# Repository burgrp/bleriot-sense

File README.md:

# BleRiot Sense

BleRiot Sense is a compact single-sensor BleRiot node built around a
`PY32F003L16S6TU` microcontroller and a PAN2110 long-range 2.4 GHz radio. Its
sensor input is configured at assembly time for one of four uses:

- A 10 kΩ B3950 NTC thermistor.
- A pulse-output flow sensor such as the YF-B10.
- A pressure sensor with a driven 0.5-5 V analog output.
- An externally powered DS18B20 digital thermometer.

The assembly population and the firmware mode must agree. The hardware does not
switch sensor modes electronically at runtime.

## Repository layout

| Path | Description |
|---|---|
| [`board/bleriot-sense.kicad_pro`](board/bleriot-sense.kicad_pro) | `PY32F003L16S6TU` hardware |
| [`fw/`](fw/README.md) | Importable Sense firmware and board-owned build profile |
| [`fw/cmd/dev/`](fw/cmd/dev/) | Local inventory and BleRiot CLI |
| [`ANALOG-INPUT.md`](ANALOG-INPUT.md) | Configurable input circuit, populations, calculations, protection, and layout |
| [`sub/hw-kicad/`](sub/hw-kicad) | Shared KiCad symbols and footprints, included as a Git submodule |

## Sensor modes

| Mode | Node measurement | Registry value |
|---|---|---|
| NTC | Averaged 12-bit ADC code | Temperature in °C |
| Flow | Rising-edge pulse count | Frequency in Hz and cumulative pulse count |
| Pressure | Averaged 12-bit ADC code | Reconstructed sensor-output voltage in V |
| DS18B20 | Up to 20 signed Q12.4 scratchpad values | Temperature registers in °C |

See [`ANALOG-INPUT.md`](ANALOG-INPUT.md) before assembling a board. It defines
the required values for `AR1`, `AR2`, `AR3`, and `AC1`, including the two
alternative flow-sensor output circuits.

The pressure transfer function and flow K-factor depend on the exact sensor.
The hub currently exposes pressure input voltage and flow frequency without
assuming undocumented sensor calibration constants.

## Firmware status

[`fw`](fw/README.md) targets the `PY32F003L16S6TU` and uses `PA0` for
the universal sensor input. The NTC path has been verified end to end on
hardware through the ADC, PAN2110 radio, MCP2210 hub dongle, BleRiot hub,
conversion layer, and Registry. The single-sensor DS18B20 path has also been
verified end to end through its 1-Wire bus and the same radio/Registry path;
multidrop behavior still requires hardware validation. Flow and pressure support build and have
host-side conversion coverage but still require mode-specific hardware tests.

DS18B20 firmware prints discovered ROM IDs over RTT at boot. A single sensor
needs no configured ID; multidrop inventories map each temperature register to
an explicit ID. See the firmware README for configuration and timing details.

The upstream TinyGo `py32f003x6` target provides the required 1 KiB system
stack. The firmware runs without a task scheduler. See the firmware README for
pin assignments, first-boot option-byte handling, configuration, and memory
constraints.

## Getting started

Initialize the shared KiCad library after cloning:

```sh
git submodule update --init --recursive
```

Open the hardware project in KiCad:

```sh
kicad board/bleriot-sense.kicad_pro
```

Configure `sensorMode` in
[`fw/cmd/dev/main.go`](fw/cmd/dev/main.go), then test and build the firmware:

```sh
go -C fw test ./...
go -C fw run ./cmd/dev node build --name sense
```

Flash with a supported SWD probe:

```sh
go -C fw run ./cmd/dev node build --name sense --flash --rtt
```

With a Registry server running, start the hub in a separate terminal:

```sh
go -C fw run ./cmd/dev hub --registry http://localhost:8080 --diagnostics rf
```

For an NTC-configured node, read live temperatures:

```bash
export REGISTRY=http://localhost:8080
reg get sense.temperature --stay
```

## Toolchain

- KiCad 10 for the hardware projects.
- Go 1.25.2 or newer for the firmware inventory, generator, tests, and hub.
- TinyGo with the Puya `py32f003x6` target.
- pyOCD with the Puya CMSIS pack and a supported SWD probe.
- An MCP2210/PAN2110 BleRiot hub dongle for RF operation.
- The [`reg`](https://github.com/burgrp/reg) Registry service and CLI.

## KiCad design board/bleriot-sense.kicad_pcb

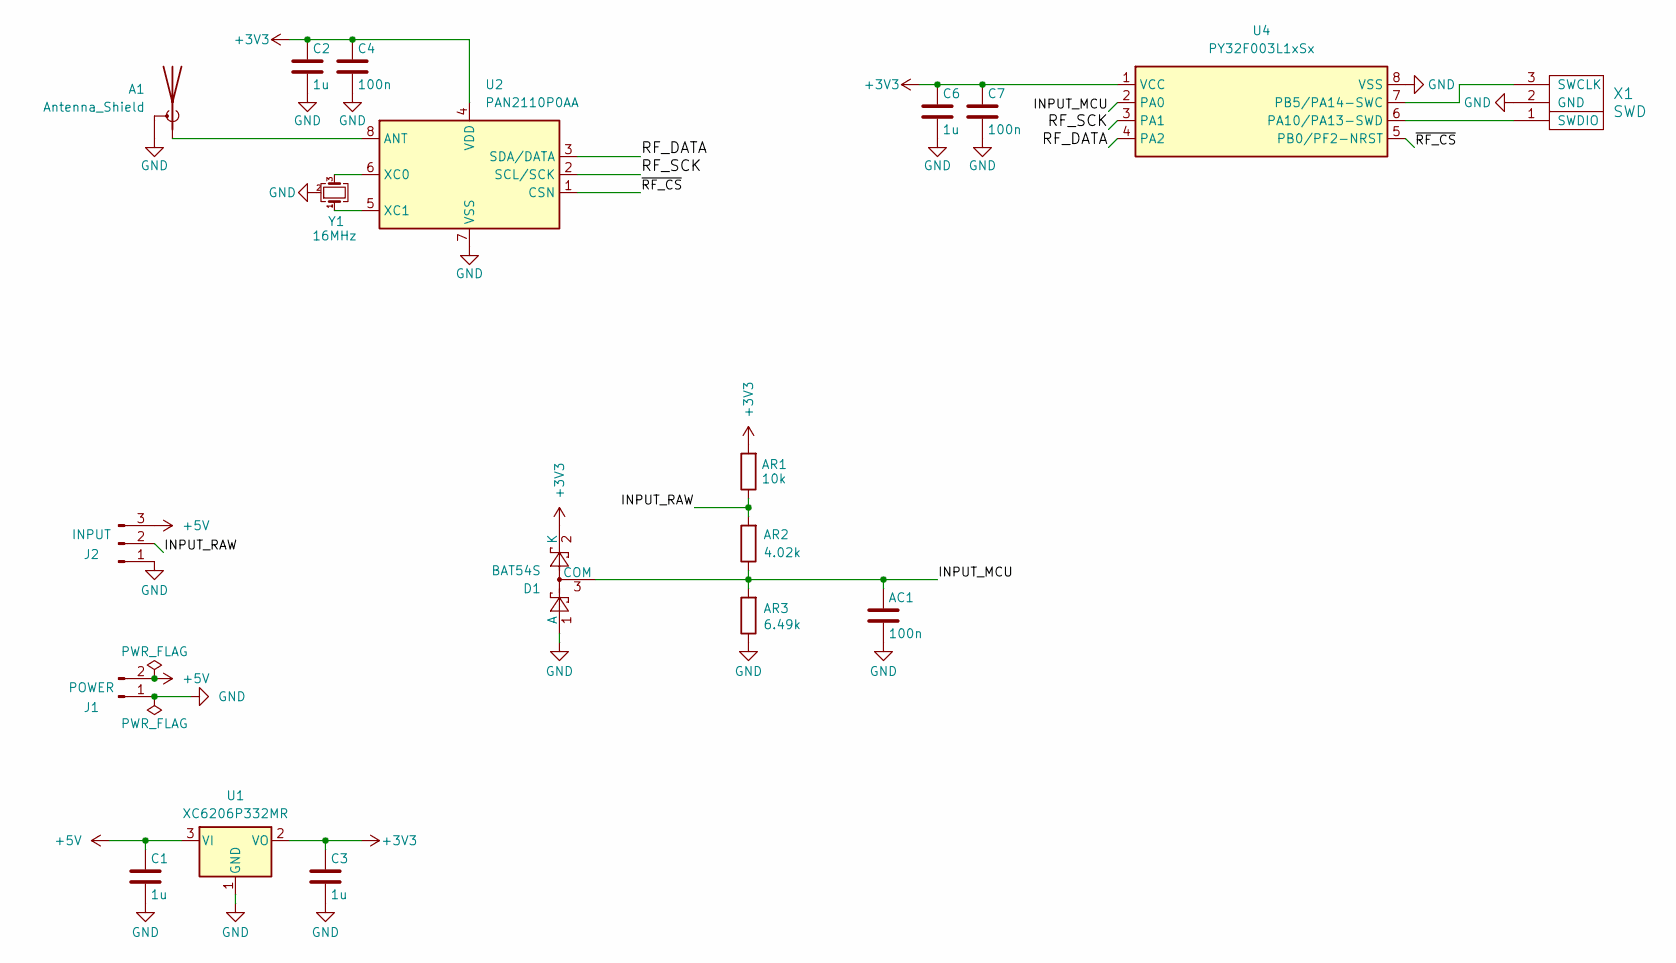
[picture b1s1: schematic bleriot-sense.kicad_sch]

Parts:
A1: Antenna_Shield; Texas_SWRA117D_2.4GHz_Left
AC1: 100n; C_0805_2012Metric
AR1: 10k; R_0805_2012Metric
AR2: 4.02k; R_0805_2012Metric
AR3: 6.49k; R_0805_2012Metric
C1, C2, C3, C6: 1u; C_0805_2012Metric
C4, C7: 100n; C_0805_2012Metric
D1: BAT54S; SOT-23
J1: POWER; PhoenixContact_MSTBA_2,5_2-G_1x02_P5.00mm_Horizontal
J2: INPUT; PhoenixContact_MSTBA_2,5_3-G_1x03_P5.00mm_Horizontal
U1: XC6206P332MR; SOT-23-3
U2: PAN2110P0AA; SOIC-8_3.9x4.9mm_P1.27mm
U4: PY32F003L1xSx; SOIC-8_3.9x4.9mm_P1.27mm
X1: SWD
Y1: 16MHz; Crystal_SMD_3225-4Pin_3.2x2.5mm

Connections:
+3V3: AR1.2, C2.1, C3.1, C4.1, C6.1, C7.1, D1.2 (K), U1.2 (VO), U2.4 (VDD), U4.1 (VCC)
+5V: C1.1, J1.2, J2.3, U1.3 (VI)
/INPUT_MCU: AC1.1, AR2.1, AR3.2, D1.3 (COM), U4.2 (PA0)
/INPUT_RAW: AR1.1, AR2.2, J2.2
/RF_DATA: U2.3 (SDA/DATA), U4.4 (PA2)
/RF_SCK: U2.2 (SCL/SCK), U4.3 (PA1)
/~RF_CS: U2.1 (CSN), U4.5 (PB0/PF2-NRST)
GND: A1.2 (Shield), AC1.2, AR3.1, C1.2, C2.2, C3.2, C4.2, C6.2, C7.2, D1.1 (A), J1.1, J2.1, U1.1 (GND), U2.7 (VSS), U4.8 (VSS), X1.2 (GND), Y1.2 (G), Y1.4 (G)
unnamed: A1.1 (A), U2.8 (ANT)
unnamed: U2.6 (XC0), Y1.3
unnamed: U2.5 (XC1), Y1.1
unnamed: U4.6 (PA10/PA13-SWD), X1.1 (SWDIO)
unnamed: U4.7 (PB5/PA14-SWC), X1.3 (SWCLK)

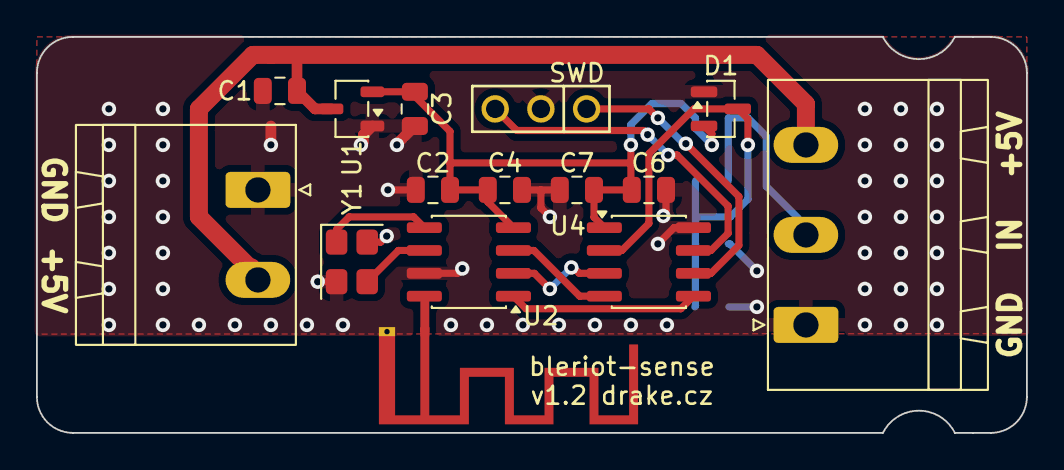
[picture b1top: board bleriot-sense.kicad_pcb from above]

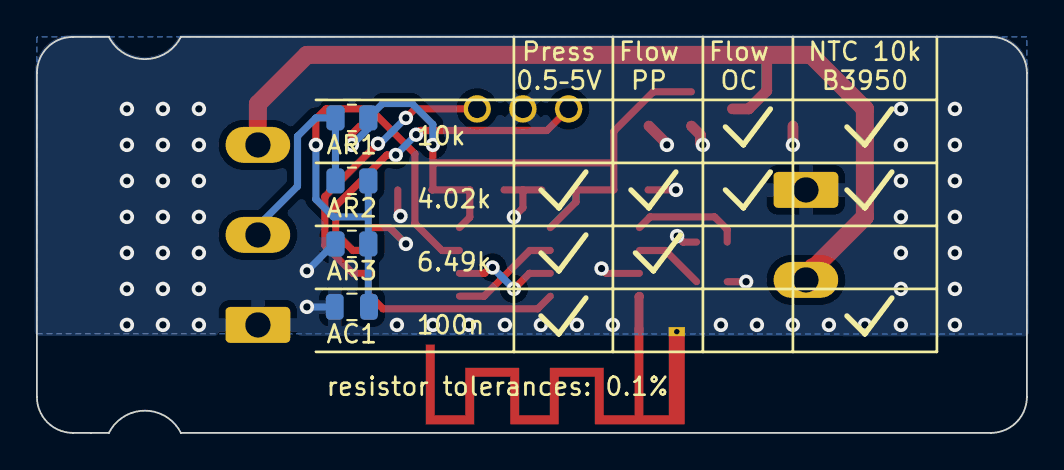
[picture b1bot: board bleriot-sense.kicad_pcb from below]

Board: 2 copper layers, 55.0 x 22.0 mm, 19 parts (4 on the bottom side), 13 nets.

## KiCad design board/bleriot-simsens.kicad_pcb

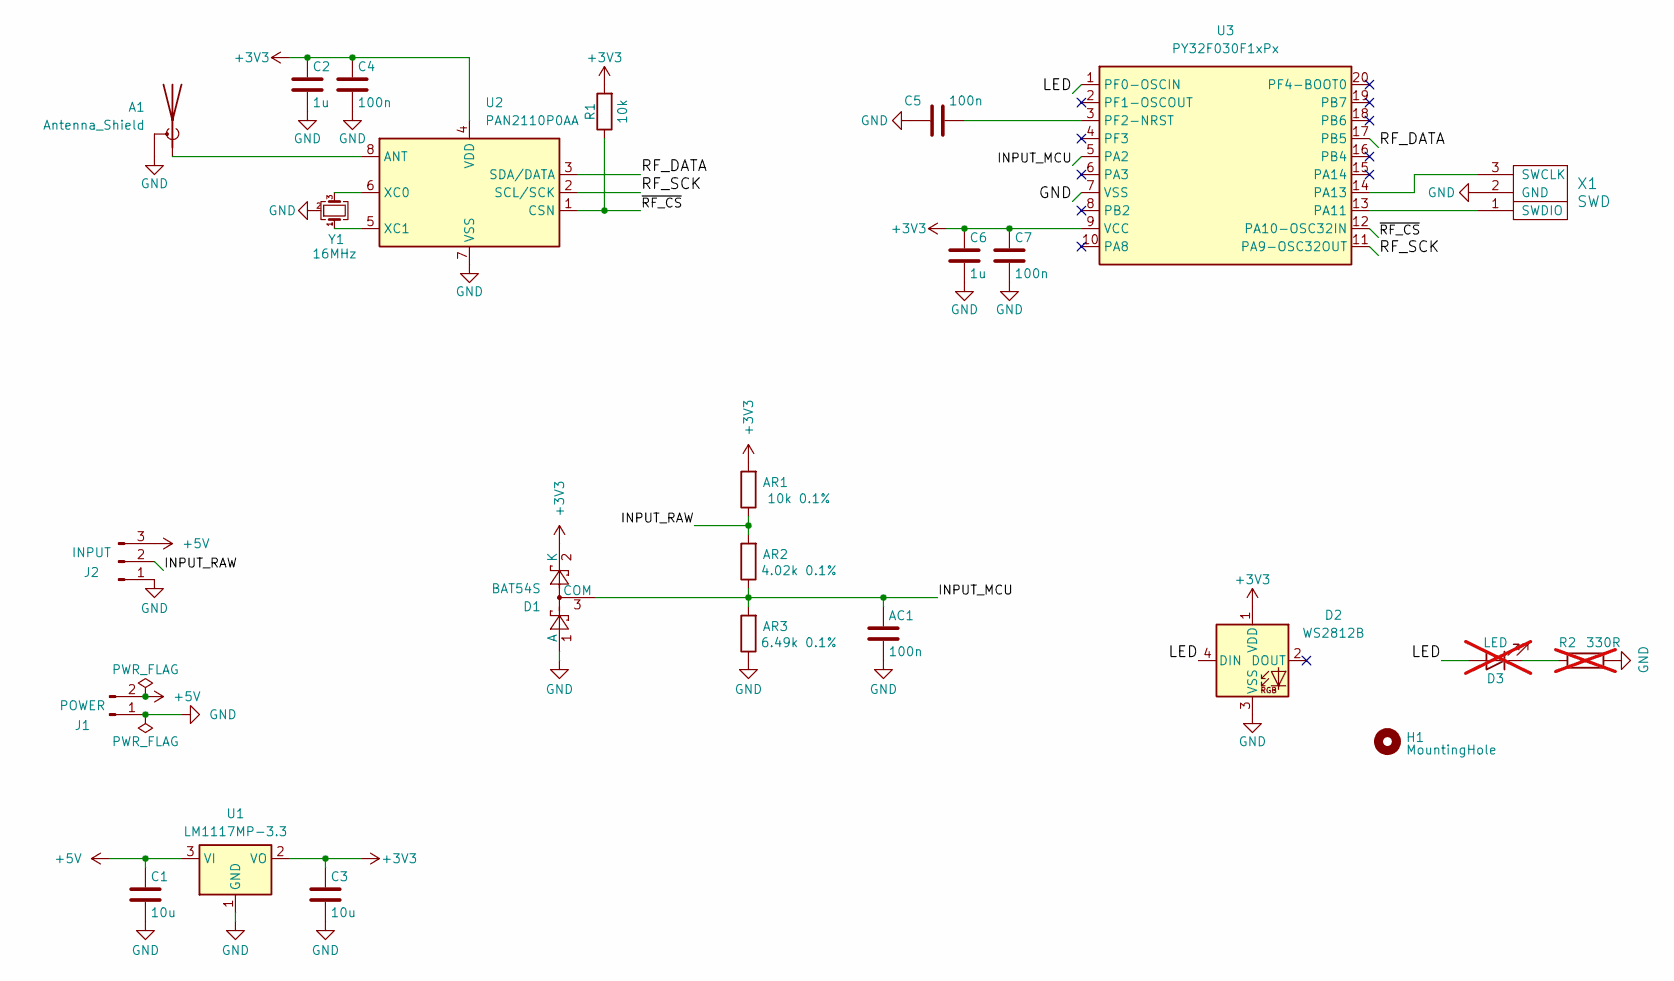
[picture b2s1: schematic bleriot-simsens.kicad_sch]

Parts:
A1: Antenna_Shield; Texas_SWRA117D_2.4GHz_Right
AC1: 100n; C_0805_2012Metric
AR1: 10k 0.1%; R_0805_2012Metric
AR2: 4.02k 0.1%; R_0805_2012Metric
AR3: 6.49k 0.1%; R_0805_2012Metric
C1, C3: 10u; C_0805_2012Metric
C2, C6: 1u; C_0805_2012Metric
C4, C5, C7: 100n; C_0805_2012Metric
D1: BAT54S; SOT-23
D2: WS2812B; LED_WS2812B_PLCC4_5.0x5.0mm_P3.2mm
D3: LED; LED_0805_2012Metric_Pad1.15x1.40mm_HandSolder; not fitted
H1: MountingHole; MountingHole_3.7mm_Pad_Via
J1: POWER; PhoenixContact_MSTBA_2,5_2-G_1x02_P5.00mm_Horizontal
J2: INPUT; PhoenixContact_MSTBA_2,5_3-G_1x03_P5.00mm_Horizontal
R1: 10k; R_0805_2012Metric
R2: 330R; R_0805_2012Metric; not fitted
U1: LM1117MP-3.3; SOT-223-3_TabPin2
U2: PAN2110P0AA; SOIC-8_3.9x4.9mm_P1.27mm
U3: PY32F030F1xPx; TSSOP-20_4.4x6.5mm_P0.65mm
X1: SWD
Y1: 16MHz; Crystal_SMD_3225-4Pin_3.2x2.5mm

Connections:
+3V3: AR1.2, C2.1, C3.1, C4.1, C6.1, C7.1, D1.2 (K), D2.1 (VDD), R1.2, U1.2 (VO), U2.4 (VDD), U3.9 (VCC)
+5V: C1.1, J1.2, J2.3, U1.3 (VI)
/INPUT_MCU: AC1.1, AR2.1, AR3.2, D1.3 (COM), U3.5 (PA2)
/INPUT_RAW: AR1.1, AR2.2, J2.2
/LED: D2.4 (DIN), D3.2 (A), U3.1 (PF0-OSCIN)
/RF_DATA: U2.3 (SDA/DATA), U3.17 (PB5)
/RF_SCK: U2.2 (SCL/SCK), U3.11 (PA9-OSC32OUT)
/~RF_CS: R1.1, U2.1 (CSN), U3.12 (PA10-OSC32IN)
GND: A1.2 (Shield), AC1.2, AR3.1, C1.2, C2.2, C3.2, C4.2, C5.2, C6.2, C7.2, D1.1 (A), D2.3 (VSS), J1.1, J2.1, R2.1, U1.1 (GND), U2.7 (VSS), U3.7 (VSS), X1.2 (GND), Y1.2 (G), Y1.4 (G)
unnamed: A1.1 (A), U2.8 (ANT)
unnamed: D3.1 (K), R2.2
unnamed: U2.6 (XC0), Y1.3
unnamed: U2.5 (XC1), Y1.1
unnamed: U3.13 (PA11), X1.1 (SWDIO)
unnamed: U3.14 (PA13), X1.3 (SWCLK)
unnamed: C5.1, U3.3 (PF2-NRST)

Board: 2 copper layers, 25 parts (0 on the bottom side), 16 nets, no tracks yet.
